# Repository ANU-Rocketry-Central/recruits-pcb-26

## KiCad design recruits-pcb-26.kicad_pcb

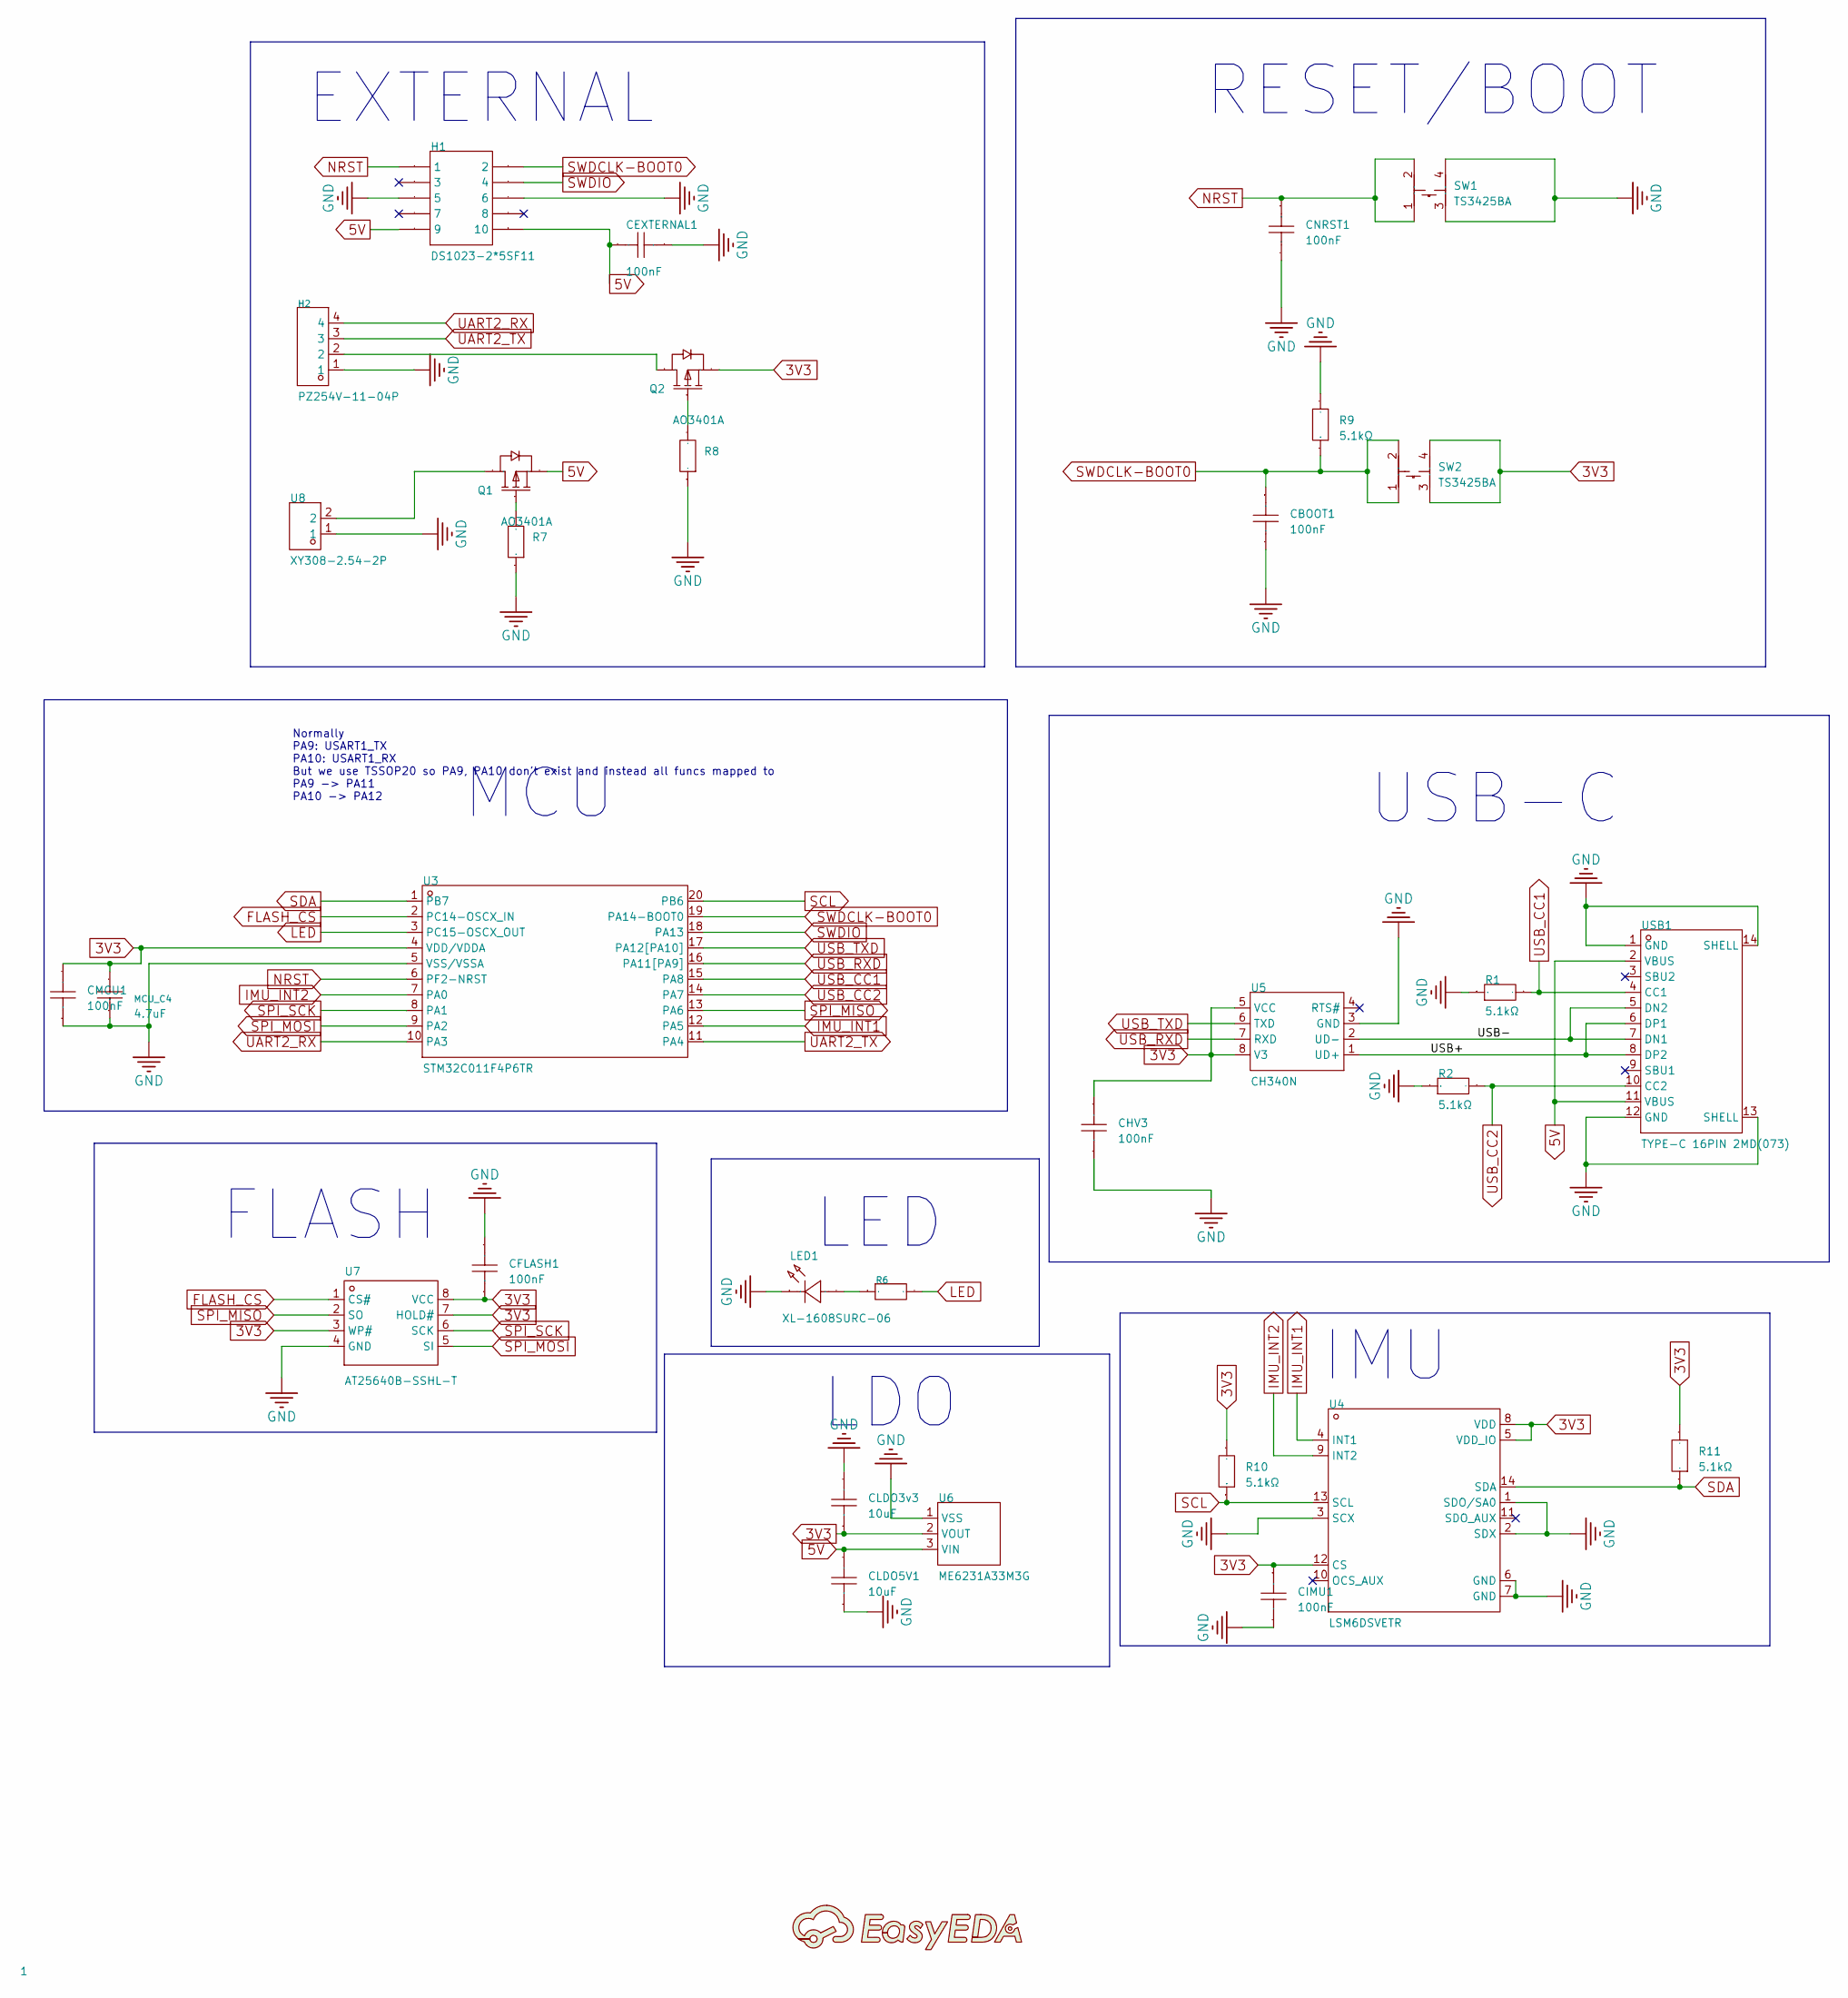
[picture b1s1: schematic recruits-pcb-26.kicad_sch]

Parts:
1: (no value)
CBOOT1: 100nF; C0805; Manufacturer Part CC0805KRX7R9BB104; LCSC Part Name 100nF ±10% 50V
CEXTERNAL1: 100nF; C0805; Manufacturer Part CC0805KRX7R9BB104; LCSC Part Name 100nF ±10% 50V
CFLASH1: 100nF; C0805; Manufacturer Part CC0805KRX7R9BB104; LCSC Part Name 100nF ±10% 50V
CHV3: 100nF; C0805; Manufacturer Part CC0805KRX7R9BB104; LCSC Part Name 100nF ±10% 50V
CIMU1: 100nF; C0805; Manufacturer Part CC0805KRX7R9BB104; LCSC Part Name 100nF ±10% 50V
CLDO3v3, CLDO5V1: 10uF; C0603; Manufacturer Part CL10A106MQ8NNNC; LCSC Part Name 10uF ±20% 6.3V
CMCU1: 100nF; C0805; Manufacturer Part CC0805KRX7R9BB104; LCSC Part Name 100nF ±10% 50V
CNRST1: 100nF; C0805; Manufacturer Part CC0805KRX7R9BB104; LCSC Part Name 100nF ±10% 50V
H1: DS1023-2*5SF11; HDR-TH_10P-P2.54-V-F-R2-C5-S2.54; Manufacturer Part DS1023-2*5SF11; LCSC Part Name 黑色 2x5P 间距:2.54mm 直插
H2: PZ254V-11-04P; HDR-TH_4P-P2.54-V-M; Manufacturer Part PZ254V-11-04P; LCSC Part Name 1x4P 间距:2.54mm 方针 直插
LED1: XL-1608SURC-06; LED0603-RD_RED; Manufacturer Part XL-1608SURC-06; LCSC Part Name 0603红色贴片式发光二极管
MCU_C4: 4.7uF; C0603; Manufacturer Part CL10A475KP8NNNC; LCSC Part Name 4.7uF ±10% 10V
Q1, Q2: AO3401A; SOT-23_L2.9-W1.3-P1.90-LS2.4-BR; Manufacturer Part AO3401A; LCSC Part Name 1个P沟道 耐压:30V 电流:4.2A
R1, R2, R9, R10, R11: 5.1kΩ; R0805; Manufacturer Part FRC0805J512TS; LCSC Part Name 5.1kΩ ±5% 125mW 厚膜电阻
R6: R0805; Manufacturer Part FRC0805J750 TS; LCSC Part Name 75Ω ±5% 125mW 厚膜电阻
R7, R8: R0805; Manufacturer Part FRC0805J104 TS; LCSC Part Name 100kΩ ±5% 125mW 厚膜电阻
SW1, SW2: TS3425BA; SW-SMD_4P-L4.2-W3.2-P2.15-LS4.6-1; Manufacturer Part TS3425BA; LCSC Part Name 4.2*3.2*2.5mm 立贴 轻触开关
U3: STM32C011F4P6TR; TSSOP-20_L6.5-W4.4-P0.65-LS6.4-BL; Manufacturer Part STM32C011F4P6TR; LCSC Part Name STM32C011F4P6TR
U4: LSM6DSVETR; LGA-14_L3.0-W2.5-P0.50-TL; Manufacturer Part LSM6DSVETR; LCSC Part Name 6轴惯性测量单元（IMU），带嵌入式传感器融合、I3C、OIS/EIS，适用于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
U5: CH340N; SOP-8_L4.9-W3.9-P1.27-LS6.0-BL; Manufacturer Part CH340N; LCSC Part Name USB2.0芯片CH340
U6: ME6231A33M3G; SOT-23-3_L2.9-W1.6-P1.90-LS2.8-BR; Manufacturer Part ME6231A33M3G; LCSC Part Name 18V 低功耗、高精度、高电源抑制比 LDO 稳压器
U7: AT25640B-SSHL-T; SOIC-8_L4.9-W3.9-P1.27-LS6.0-BL; Manufacturer Part AT25640B-SSHL-T; LCSC Part Name SPI 串行 EEPROM
U8: XY308-2.54-2P; CONN-TH_XY308-2.54-2P; Manufacturer Part XY308-2.54-2P; LCSC Part Name 1x2P 2.54mm 直插 排数:1 每排P数:2
USB1: TYPE-C 16PIN 2MD(073); USB-C-SMD_TYPE-C-6PIN-2MD-073; Manufacturer Part TYPE-C 16PIN 2MD(073); LCSC Part Name 16P卧贴母座

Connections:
3V3: CFLASH1.1, CHV3.2, CIMU1.1, CLDO3v3.1, CMCU1.2, MCU_C4.2, Q2.2 (S), R10.2, R11.2, SW2.3, SW2.4, U3.4 (VDD/VDDA), U4.5 (VDD_IO), U4.8 (VDD), U4.12 (CS), U5.5 (VCC), U5.8 (V3), U6.2 (VOUT), U7.3 (WP#), U7.7 (HOLD#), U7.8 (VCC)
5V: CEXTERNAL1.2, CLDO5V1.2, H1.10, Q1.2 (S), U6.3 (VIN), USB1.2 (VBUS), USB1.11 (VBUS)
/USB+: U5.1 (UD+), USB1.6 (DP1), USB1.8 (DP2)
/USB-: U5.2 (UD-), USB1.5 (DN2), USB1.7 (DN1)
FLASH_CS: U3.2 (PC14-OSCX_IN), U7.1 (CS#)
GND: CBOOT1.2, CEXTERNAL1.1, CFLASH1.2, CHV3.1, CIMU1.2, CLDO3v3.2, CLDO5V1.1, CMCU1.1, CNRST1.2, H1.5, H1.6, H2.1, LED1.1 (K), MCU_C4.1, R1.1, R2.1, R7.1, R8.1, R9.2, SW1.3, SW1.4, U3.5 (VSS/VSSA), U4.1 (SDO/SA0), U4.2 (SDX), U4.3 (SCX), U4.6 (GND), U4.7 (GND), U5.3 (GND), U6.1 (VSS), U7.4 (GND), U8.1, USB1.1 (GND), USB1.12 (GND), USB1.13 (SHELL), USB1.14 (SHELL)
IMU_INT1: U3.12 (PA5), U4.4 (INT1)
IMU_INT2: U3.7 (PA0), U4.9 (INT2)
LED: R6.2, U3.3 (PC15-OSCX_OUT)
NRST: CNRST1.1, H1.1, SW1.1, SW1.2, U3.6 (PF2-NRST)
unnamed: LED1.2 (A), R6.1
unnamed: Q1.3 (D), U8.2
unnamed: Q1.1 (G), R7.2
unnamed: H2.2, Q2.3 (D)
unnamed: Q2.1 (G), R8.2
SCL: R10.1, U3.20 (PB6), U4.13 (SCL)
SDA: R11.1, U3.1 (PB7), U4.14 (SDA)
SPI_MISO: U3.13 (PA6), U7.2 (SO)
SPI_MOSI: U3.9 (PA2), U7.5 (SI)
SPI_SCK: U3.8 (PA1), U7.6 (SCK)
SWDCLK-BOOT0: CBOOT1.1, H1.2, R9.1, SW2.1, SW2.2, U3.19 (PA14-BOOT0)
SWDIO: H1.4, U3.18 (PA13)
UART2_RX: H2.4, U3.10 (PA3)
UART2_TX: H2.3, U3.11 (PA4)
USB_CC1: R1.2, U3.15 (PA8), USB1.4 (CC1)
USB_CC2: R2.2, U3.14 (PA7), USB1.10 (CC2)
USB_RXD: U3.16 (PA11[PA9]), U5.7 (RXD)
USB_TXD: U3.17 (PA12[PA10]), U5.6 (TXD)

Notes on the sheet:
LDO
IMU
FLASH
LED
EXTERNAL
USB-C
Normally PA9: USART1_TX PA10: USART1_RX But we use TSSOP20 so PA9, PA10 don't exist and instead all funcs mapped to PA9 -> PA11 PA10 -> PA12
MCU
RESET/BOOT

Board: 4 copper layers, 32 parts (0 on the bottom side), 28 nets, no tracks yet.
